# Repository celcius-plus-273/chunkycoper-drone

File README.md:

# chunkycoper-drone

Repository to host all of the design files regarding my quadcopter drone project.

The repository is broken down into three main sections:
1. Electronic Design Files (boards)
2. Code & Firmware (control)
3. Mechanical Design Files (shell)

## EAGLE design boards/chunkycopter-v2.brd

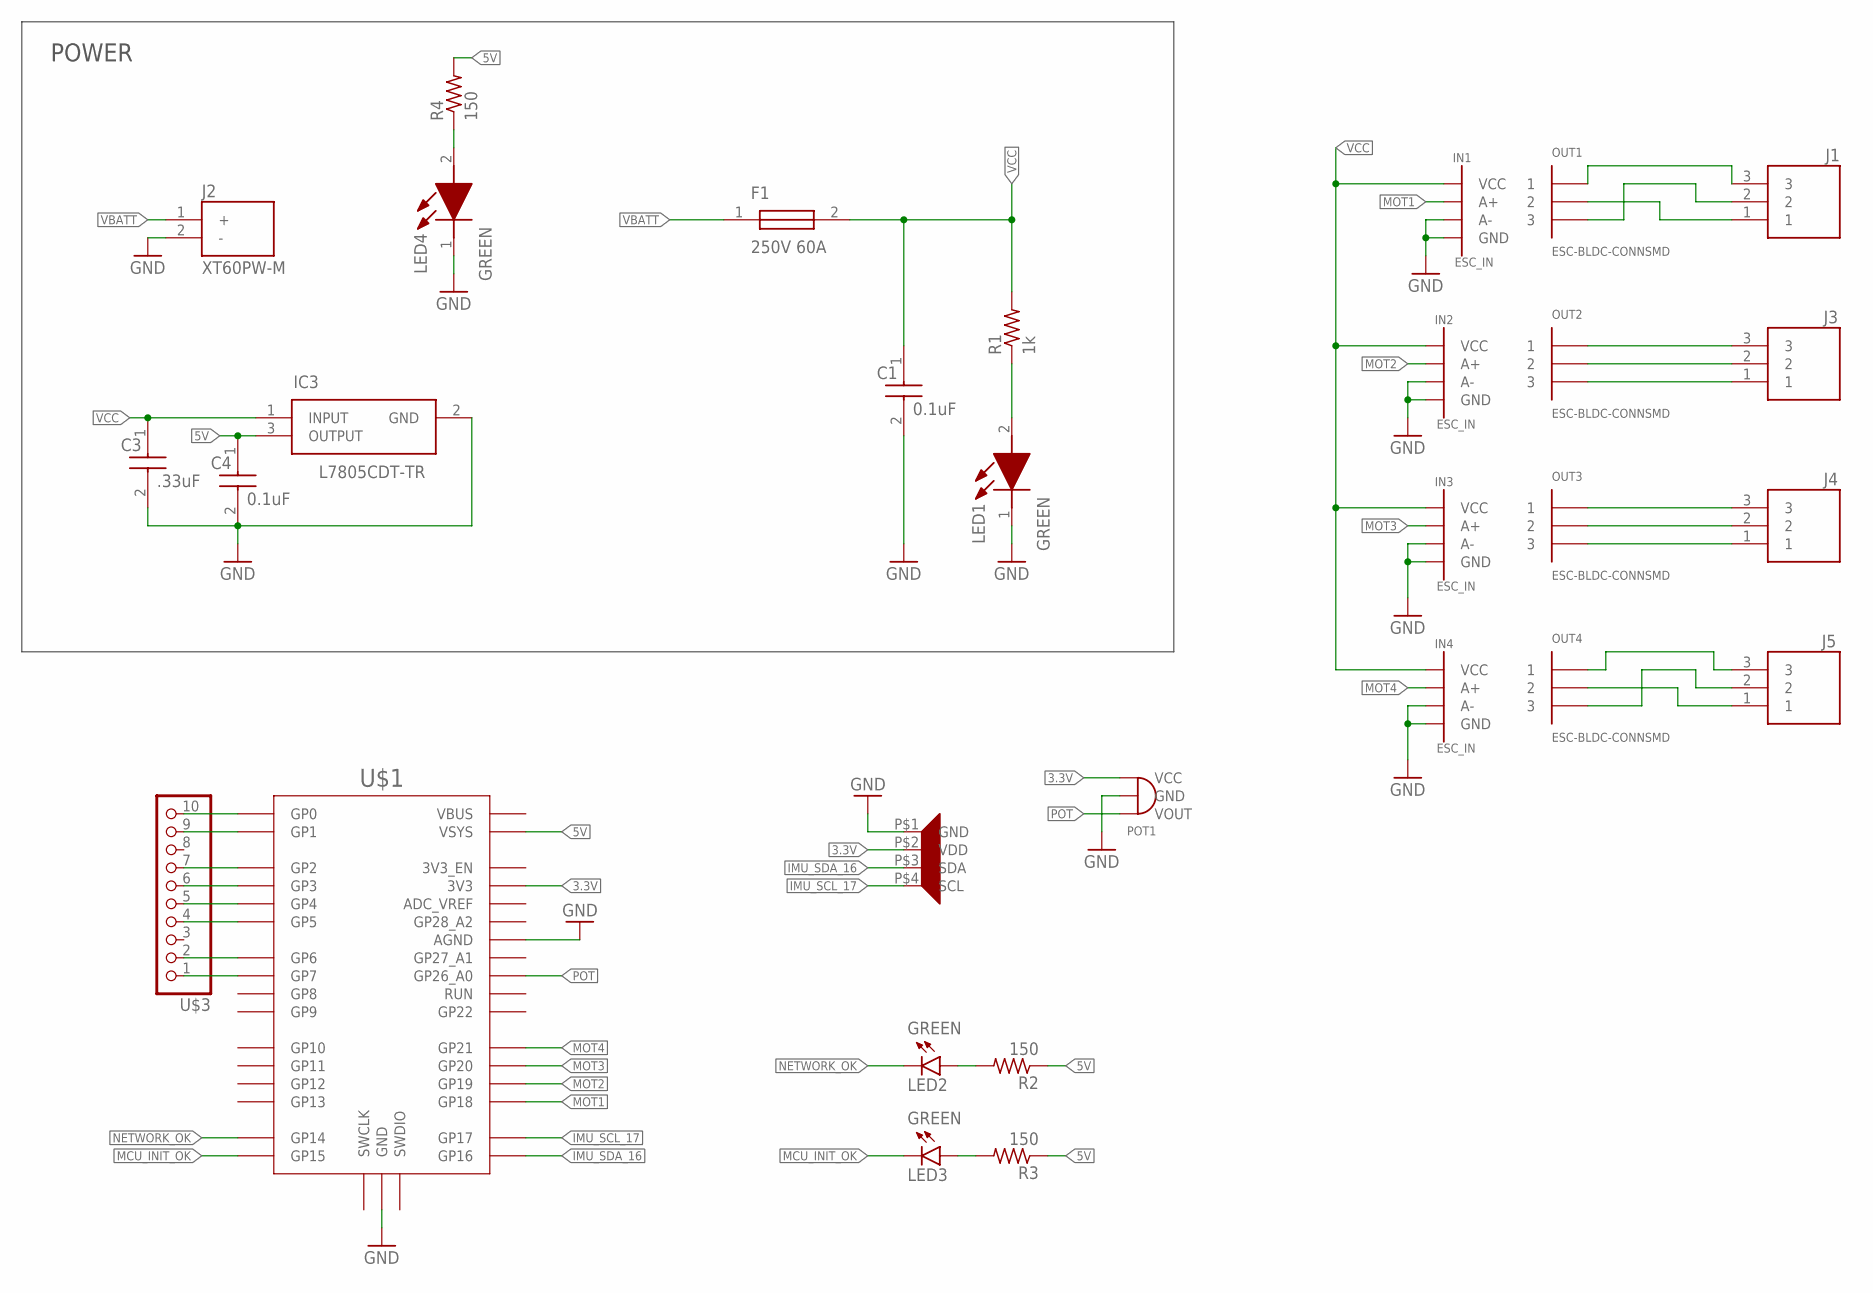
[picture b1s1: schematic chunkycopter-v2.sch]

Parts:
C1, C4: 0.1uF; C0805
C3: .33uF; C0805
F1: 250V 60A; 0456060DRSDE
IC3: L7805CDT-TR; L7805CDTTR
IN1, IN2, IN3, IN4: ESC_IN; ESC-INPUT
J1, J3, J4, J5: MOLEX-CONN-39-30-3037; 39303037
J2: XT60PW-M; AMASS_XT60PW-M
LED1, LED4: GREEN; SML012ENTT86
LED2, LED3: GREEN; CHIPLED_0603
OUT1, OUT2, OUT3, OUT4: ESC-BLDC-CONNSMD; ESC-OUT
POT1: POT-CONN; POT
R1: 1k; R0805
R2, R3, R4: 150; R0805
U$1: RPI_PICO-TH; RPI_PICO_TH
U$2: LSM9DS1_IMU
U$3: PINHD-1X10; 1X10-BIG

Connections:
3.3V: POT1.P_VCC (VCC), U$1.3V3, U$2.P$2 (VDD)
5V: C4.1, IC3.3 (OUTPUT), R2.1, R3.1, R4.2, U$1.VSYS
GND: C1.2, C3.2, C4.2, IC3.2 (GND), IN1.A-, IN1.GND, IN2.A-, IN2.GND, IN3.A-, IN3.GND, IN4.A-, IN4.GND, J2.2 (-), LED1.1 (K), LED4.1 (K), POT1.P_GND (GND), U$1.AGND, U$1.GND@1 (GND), U$1.GND@2 (GND), U$1.GND@3 (GND), U$1.GND@4 (GND), U$1.GND@5 (GND), U$1.GND@6 (GND), U$1.GND@7 (GND), U$1.GND@8 (GND), U$2.P$1 (GND)
IMU_SCL_17: U$1.GP17, U$2.P$4 (SCL)
IMU_SDA_16: U$1.GP16, U$2.P$3 (SDA)
MCU_INIT_OK: LED3.C, U$1.GP15
MOT1: IN1.A+, U$1.GP18
MOT2: IN2.A+, U$1.GP19
MOT3: IN3.A+, U$1.GP20
MOT4: IN4.A+, U$1.GP21
unnamed: LED1.2 (A), R1.1
unnamed: J1.3, OUT1.1
unnamed: J1.2, OUT1.3
unnamed: J1.1, OUT1.2
unnamed: J3.3, OUT2.1
unnamed: J3.2, OUT2.2
unnamed: J3.1, OUT2.3
unnamed: J4.3, OUT3.1
unnamed: J5.3, OUT4.1
unnamed: J4.1, OUT3.3
unnamed: J5.1, OUT4.2
unnamed: J5.2, OUT4.3
unnamed: U$1.GP0, U$3.10
unnamed: U$1.GP1, U$3.9
unnamed: J4.2, OUT3.2
unnamed: U$1.GP2, U$3.7
unnamed: U$1.GP3, U$3.6
unnamed: U$1.GP4, U$3.5
unnamed: U$1.GP5, U$3.4
unnamed: U$1.GP6, U$3.2
unnamed: U$1.GP7, U$3.1
unnamed: LED2.A, R2.2
unnamed: LED3.A, R3.2
unnamed: LED4.2 (A), R4.1
NETWORK_OK: LED2.C, U$1.GP14
POT: POT1.P_VOUT (VOUT), U$1.GP26_A0
VBATT: F1.1, J2.1 (+)
VCC: C1.1, C3.1, F1.2, IC3.1 (INPUT), IN1.VCC, IN2.VCC, IN3.VCC, IN4.VCC, R1.2

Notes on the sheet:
POWER

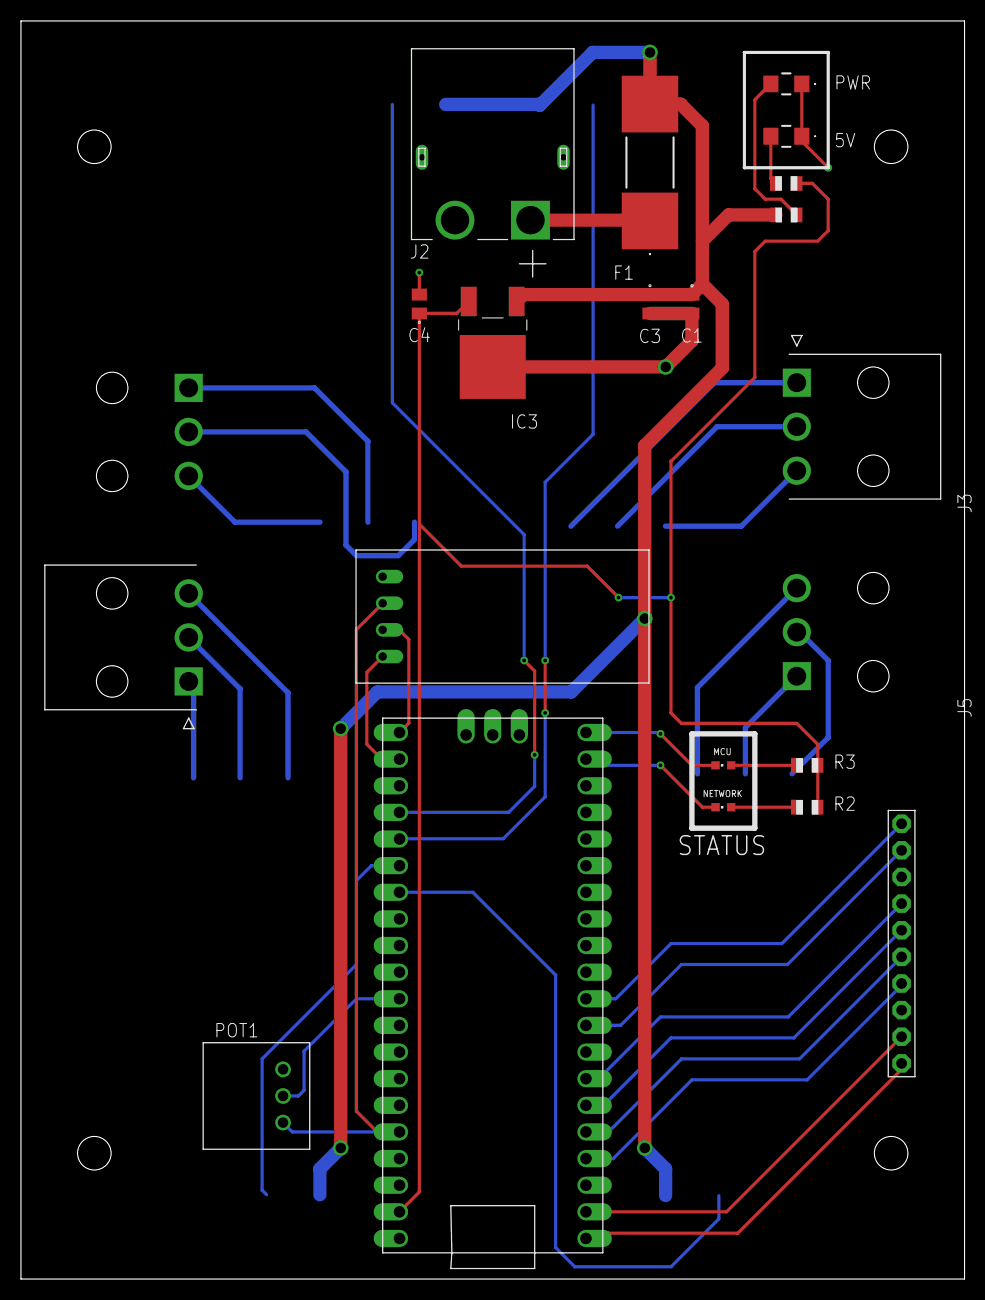
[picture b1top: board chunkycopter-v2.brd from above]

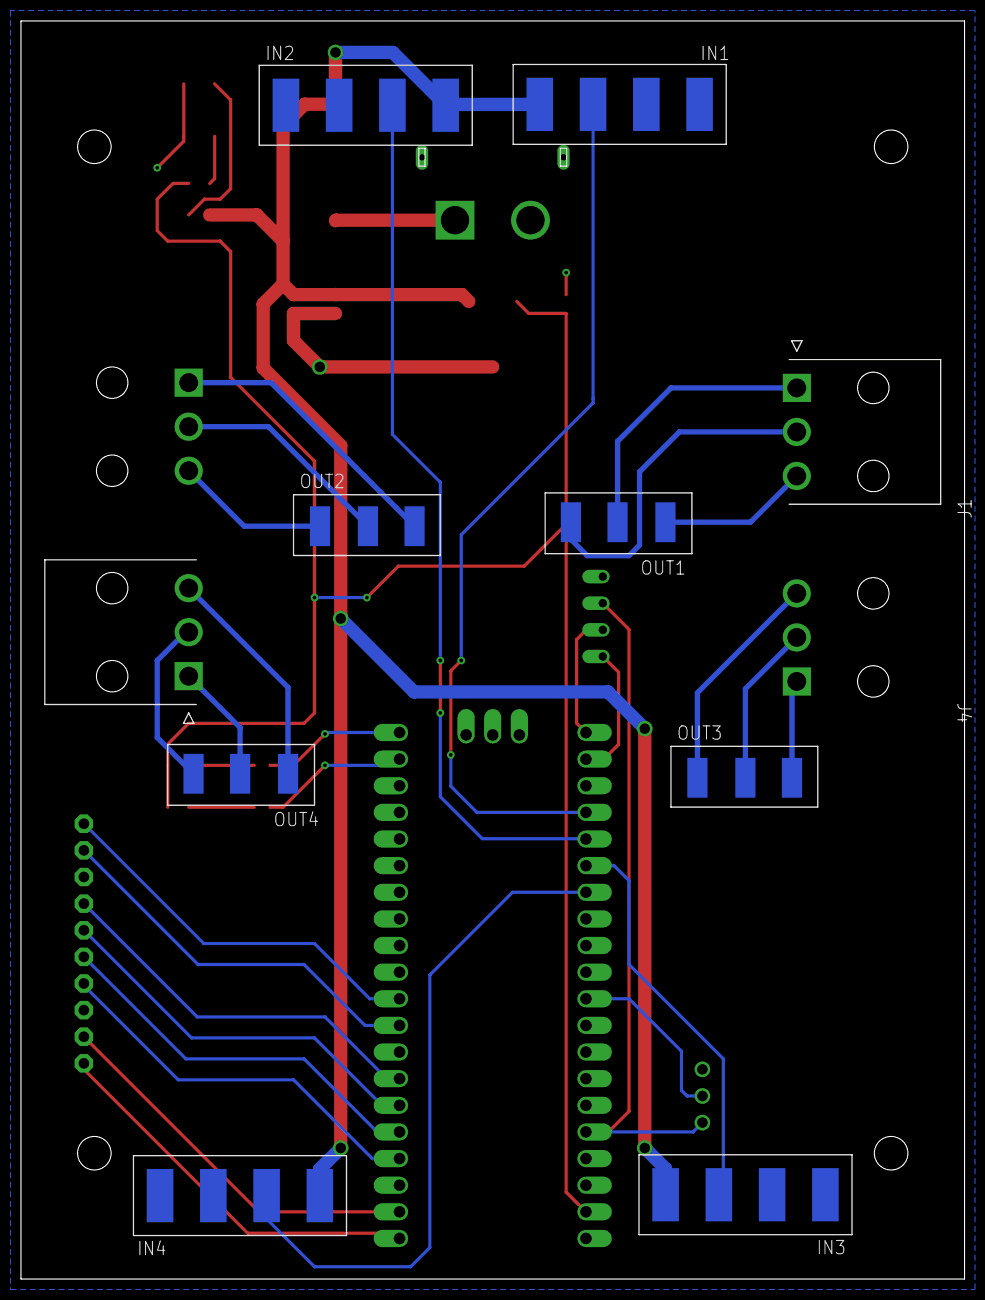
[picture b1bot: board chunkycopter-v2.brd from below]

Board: 2 copper layers, 90.0 x 120.0 mm, 30 parts (10 on the bottom side), 38 nets.

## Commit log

2023-06-24 added eagle design files
2023-06-24 added upython files and imu driver
2023-06-25 reorganized repo files
2023-06-25 testing if deleting works
2023-06-25 deleted duplicated files
2023-06-25 Create README.md for control directory
2023-06-25 Create README.md for pcb directory
2023-06-25 added stl 3d design files
2023-12-16 added esc kicad project
2023-12-16 updated readme a little bit
2023-12-16 renamed the directories
2023-12-16 updated readme oreder
2023-12-30 updated MOSFETs
2023-12-30 finished layout and schematic
2023-12-31 simplified PHASE A circuit
2024-01-01 started simplified esc
2024-01-02 added MIC4606 and IRFR mosfet
2024-01-03 changed TVS diode
2024-01-03 finished esc simple schematic
2024-01-09 modified git ignore
